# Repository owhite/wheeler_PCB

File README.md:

# wheeler_PCB
[Link to spreadsheet](https://docs.google.com/spreadsheets/d/1u32QXF2sBAJVFp-kBQT08TGvSo9xbbkm4VCSQnjvcI0/edit#gid=474216127)

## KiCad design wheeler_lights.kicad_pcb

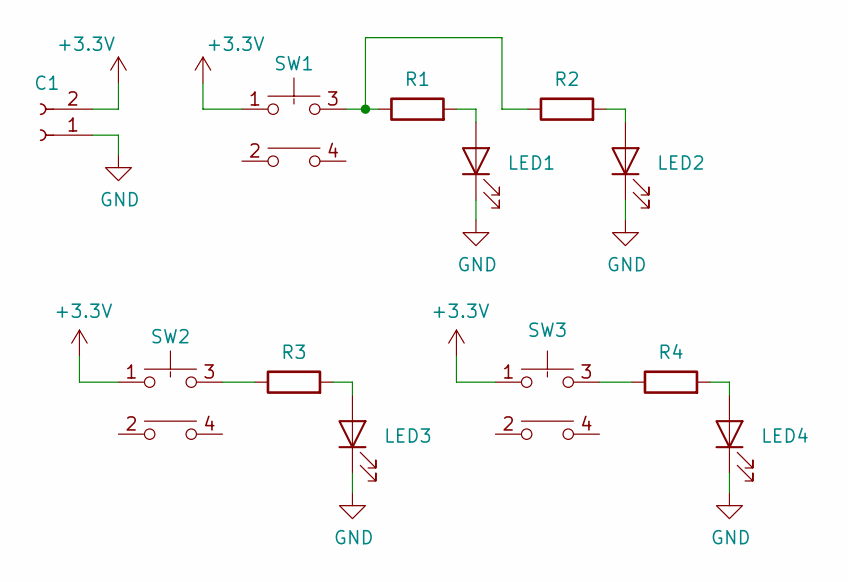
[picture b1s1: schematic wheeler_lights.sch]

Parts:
C1: Conn_01x02_Female; PinHeader_1x02_P2.54mm_Vertical
LED1, LED2, LED3, LED4: LED; LED_1206_3216Metric_Pad1.42x1.75mm_HandSolder
R1, R2, R3, R4: R; R_1210_3225Metric_Pad1.42x2.65mm_HandSolder
SW1, SW2, SW3: SW_Push_Dual; SW_PUSH_6.5mm_H4.5mm

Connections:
+3V3: C1.2, SW1.1, SW2.1, SW3.1
GND: C1.1, LED1.1 (K), LED2.1 (K), LED3.1 (K), LED4.1 (K)
unnamed: LED1.2 (A), R1.2
unnamed: LED2.2 (A), R2.2
unnamed: LED3.2 (A), R3.2
unnamed: LED4.2 (A), R4.2
unnamed: R1.1, R2.1, SW1.3
unnamed: R3.1, SW2.3
unnamed: R4.1, SW3.3

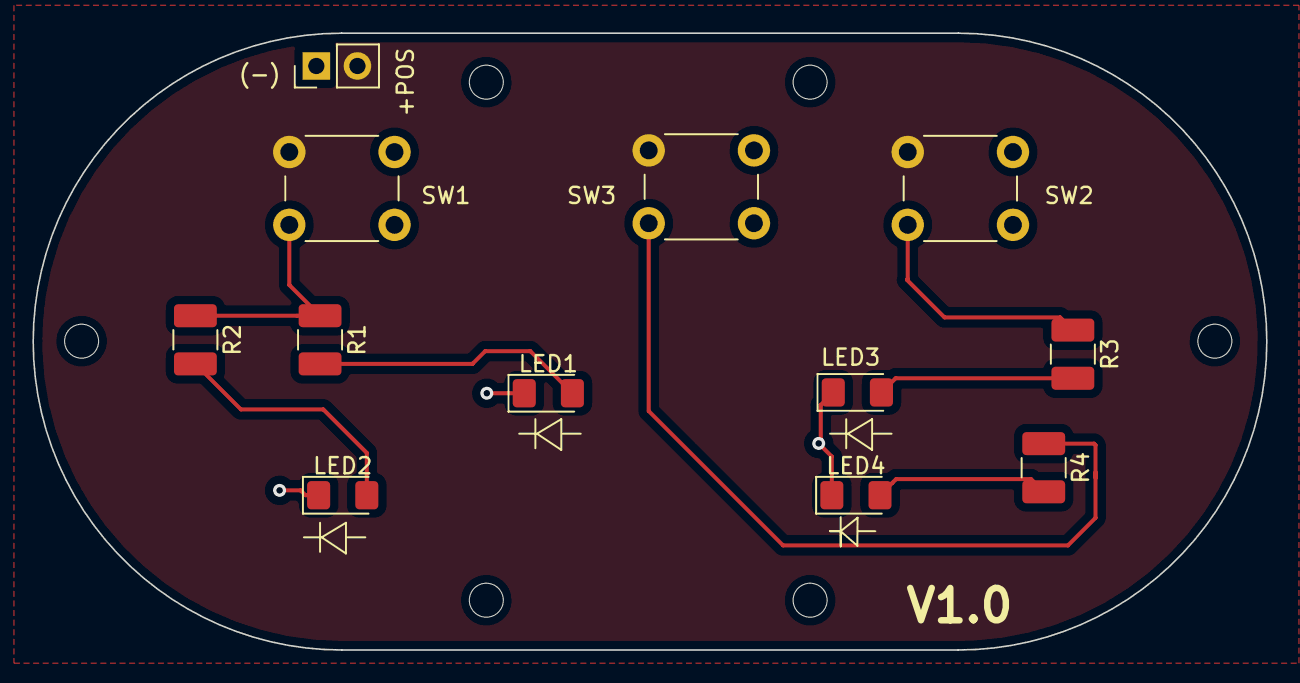
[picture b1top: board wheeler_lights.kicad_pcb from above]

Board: 2 copper layers, 76.2 x 38.1 mm, 12 parts (0 on the bottom side), 9 nets.

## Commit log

2022-06-24 added link
